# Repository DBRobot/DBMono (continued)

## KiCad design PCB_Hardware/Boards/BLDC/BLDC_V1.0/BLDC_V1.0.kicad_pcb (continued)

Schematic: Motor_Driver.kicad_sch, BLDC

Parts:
C15: 1u; C_0603_1608Metric; Manufacturer_Part_Number CC0603ZRY5V6BB105
C16: 47n; C_0805_2012Metric; Manufacturer_Part_Number CL21B473KCFNNNE
C17: 100n; C_0402_1005Metric; Manufacturer_Part_Number GRM155R62A104KE14D
C18, C19, C20: 1u; C_0402_1005Metric; Manufacturer_Part_Number CL05A105MQ5NNNC
C21: 100n; C_0402_1005Metric; Manufacturer_Part_Number CC0402ZRY5V6BB104
C22, C25, C26: 2.2u; C_0805_2012Metric; Manufacturer_Part_Number GRM21BD72A225ME01L
C23: 330u; CP_Radial_D12.5mm_P5.00mm
C28: 100n; C_0805_2012Metric; Manufacturer_Part_Number C0805C104K1RACAUTO
C47, C48, C49: ?; C_0402_1005Metric; not fitted
D15, D16, D17: SMCJ90A; D_SMC
H5, H6, H7: MountingHole_Pad; MountingHole_3.2mm_M3_DIN965_Pad
Q3, Q4, Q5, Q6, Q7, Q8: TPH3R70APL; SOP AdvanceN_TOS; Manufacturer_Part_Number TPH3R70APL
R12, R13, R14: 1m; R_2512_6332Metric; Manufacturer_Part_Number LR122WF100NT4E
R15, R16: 1k; R_0402_1005Metric; Manufacturer_Part_Number CQ02WGJ0102TCE
R32, R37, R38: 0; R_0402_1005Metric; Manufacturer_Part_Number RC0402JR-130RL
U1: DRV8353SRTAR; QFN-40-1EP_6x6mm_P0.5mm_EP4.6x4.6mm; Manufacturer_Part_Number DRV8353SRTAR

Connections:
+3.3V: R15.2, R16.2; also elsewhere on the board
+3.3VA: C20.1, C21.1, U1.24 (VREF); also elsewhere on the board
+BATT: C15.1, C17.1, C22.1, C23.1, C25.1, C26.1, C28.1, Q3.5 (D), Q3.6 (D), Q3.7 (D), Q3.8 (D), Q5.5 (D), Q5.6 (D), Q5.7 (D), Q5.8 (D), Q7.5 (D), Q7.6 (D), Q7.7 (D), Q7.8 (D), U1.3 (VM), U1.4 (VDRAIN); also elsewhere on the board
/MCU/DRIVER_CSN: U1.30 (nSCS); also elsewhere on the board
/MCU/DRIVER_MISO: R16.1, U1.27 (SDO); also elsewhere on the board
/MCU/DRIVER_MOSI: U1.28 (SDI); also elsewhere on the board
/MCU/DRIVER_SCLK: U1.29 (SCLK); also elsewhere on the board
/MCU/ENABLE: U1.31 (ENABLE); also elsewhere on the board
/MCU/INHA: U1.32 (INHA); also elsewhere on the board
/MCU/INHB: U1.34 (INHB); also elsewhere on the board
/MCU/INHC: U1.36 (INHC); also elsewhere on the board
/MCU/INLA: U1.33 (INLA); also elsewhere on the board
/MCU/INLB: U1.35 (INLB); also elsewhere on the board
/MCU/INLC: U1.37 (INLC); also elsewhere on the board
/MCU/SOA: C47.1, R38.2; also elsewhere on the board
/MCU/SOB: C48.1, R37.2; also elsewhere on the board
/MCU/SOC: C49.1, R32.2; also elsewhere on the board
/MCU/nFAULT: R15.1, U1.26 (nFAULT); also elsewhere on the board
GND: C17.2, C18.2, C19.2, C20.2, C21.2, C22.2, C23.2, C25.2, C26.2, C28.2, C47.2, C48.2, C49.2, D15.2 (A), D16.2 (A), D17.2 (A), R12.1, R13.1, R14.1, U1.10 (SNA), U1.11 (SNB), U1.20 (SNC), U1.25 (AGND), U1.39 (GND), U1.41 (PAD); also elsewhere on the board
unnamed: D15.1 (K), H5.1 (1_1), Q3.1 (S), Q3.2 (S), Q3.3 (S), Q4.5 (D), Q4.6 (D), Q4.7 (D), Q4.8 (D), U1.7 (SHA)
unnamed: D16.1 (K), H6.1 (1_1), Q5.1 (S), Q5.2 (S), Q5.3 (S), Q6.5 (D), Q6.6 (D), Q6.7 (D), Q6.8 (D), U1.14 (SHB)
unnamed: D17.1 (K), H7.1 (1_1), Q7.1 (S), Q7.2 (S), Q7.3 (S), Q8.5 (D), Q8.6 (D), Q8.7 (D), Q8.8 (D), U1.17 (SHC)
unnamed: Q3.4 (G), U1.6 (GHA)
unnamed: Q4.4 (G), U1.8 (GLA)
unnamed: Q5.4 (G), U1.15 (GHB)
unnamed: Q6.4 (G), U1.13 (GLB)
unnamed: Q7.4 (G), U1.16 (GHC)
unnamed: Q8.4 (G), U1.18 (GLC)
unnamed: C16.2, U1.2 (CPH)
unnamed: C16.1, U1.1 (CPL)
unnamed: C19.1, U1.38 (DVDD)
unnamed: R38.1, U1.23 (SOA)
unnamed: R37.1, U1.22 (SOB)
unnamed: R32.1, U1.21 (SOC)
unnamed: Q4.1 (S), Q4.2 (S), Q4.3 (S), R12.2, U1.9 (SPA)
unnamed: Q6.1 (S), Q6.2 (S), Q6.3 (S), R13.2, U1.12 (SPB)
unnamed: Q8.1 (S), Q8.2 (S), Q8.3 (S), R14.2, U1.19 (SPC)
unnamed: C15.2, U1.5 (VCP)
unnamed: C18.1, U1.40 (VGLS)

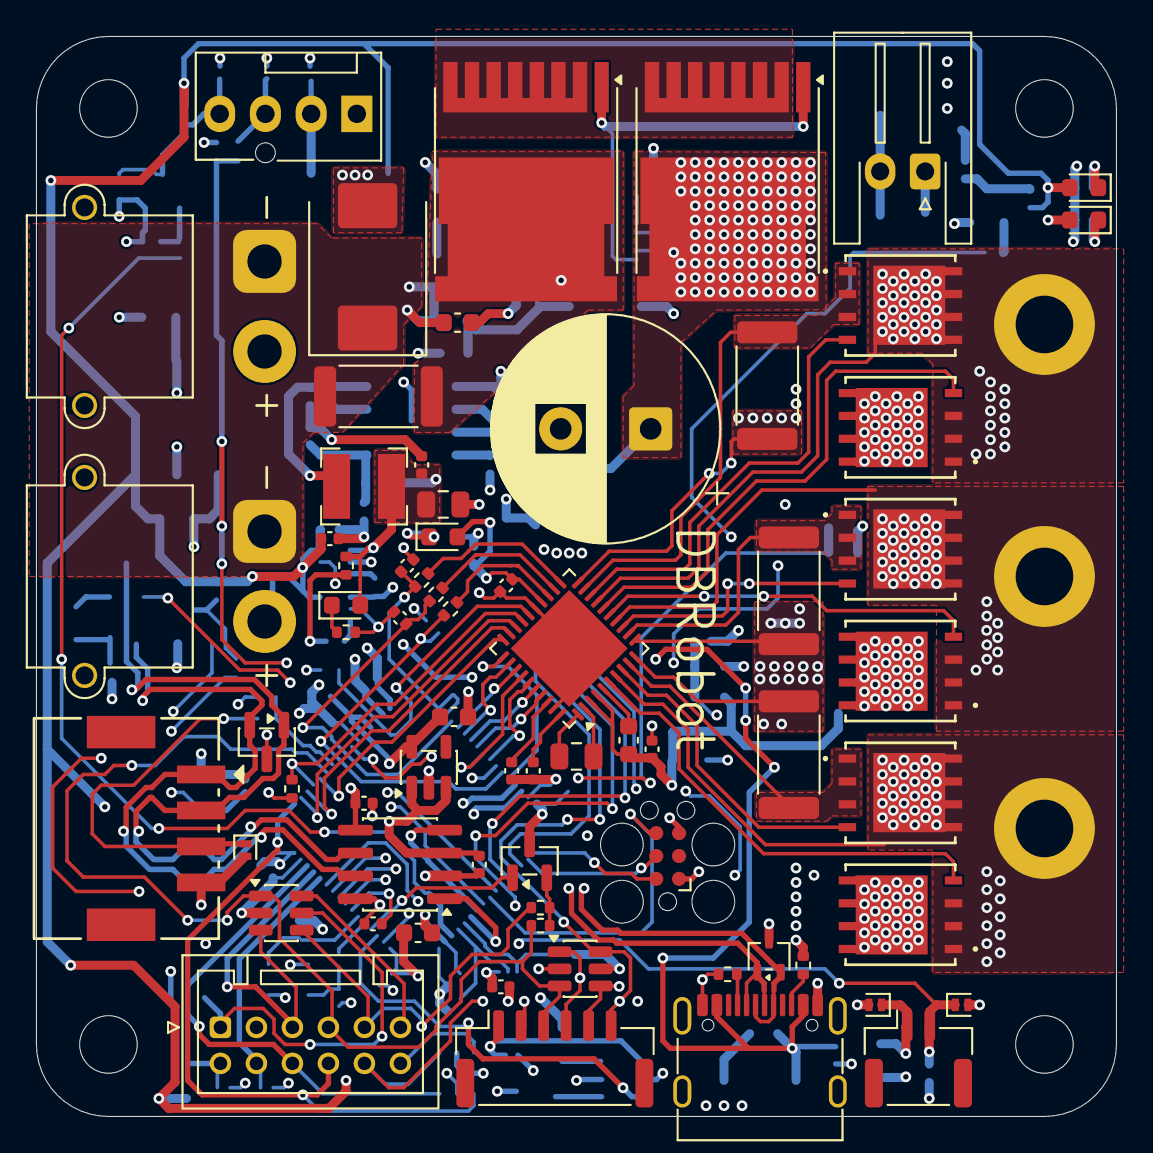
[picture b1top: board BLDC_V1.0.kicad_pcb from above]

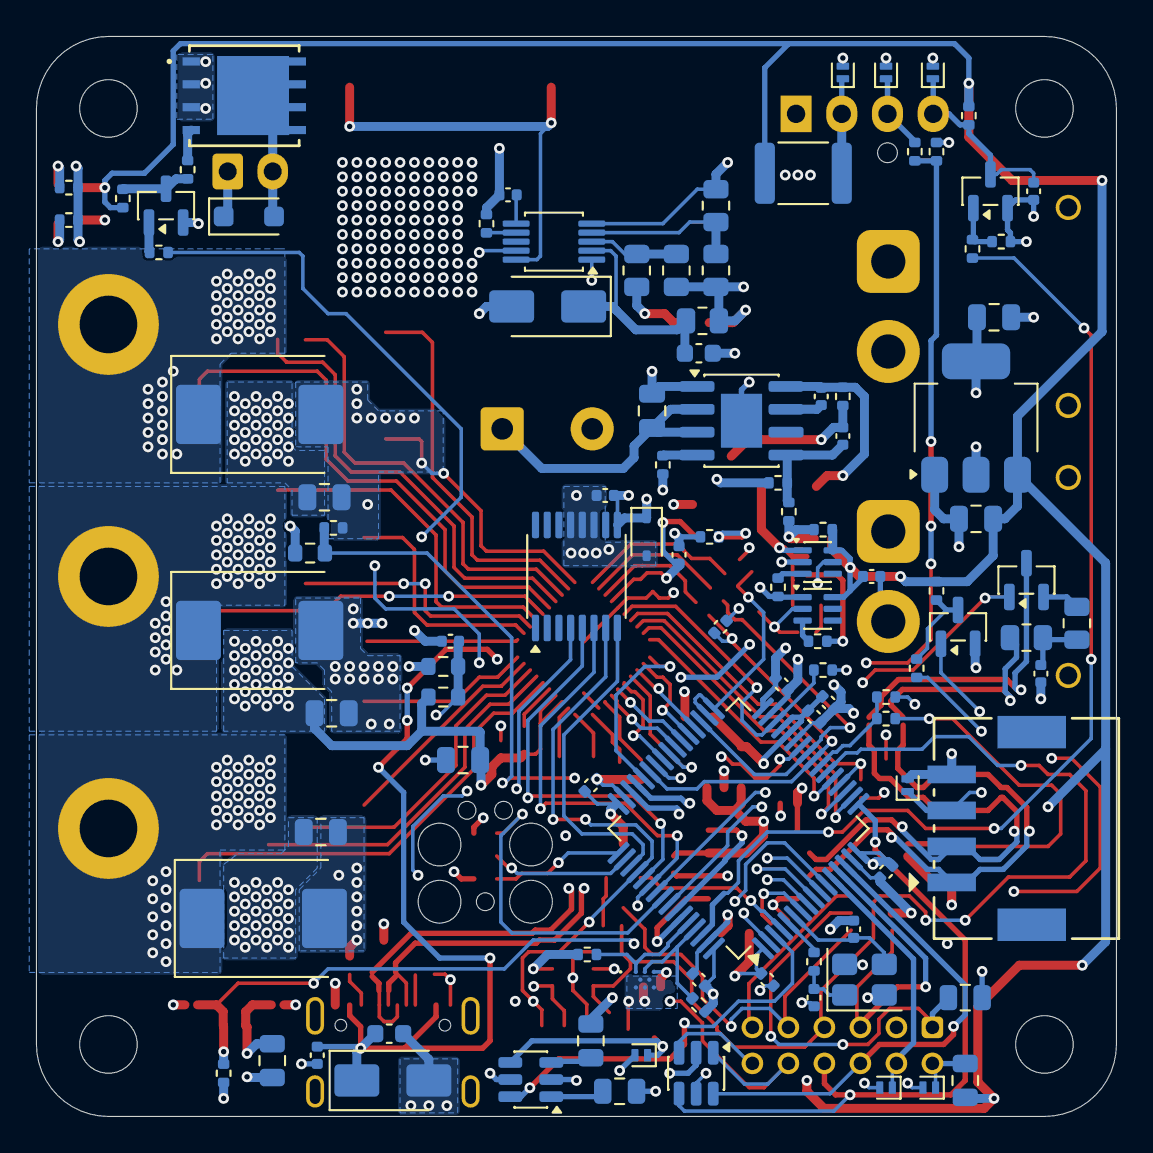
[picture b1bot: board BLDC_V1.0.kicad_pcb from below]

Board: 4 copper layers, 60.0 x 60.0 mm, 180 parts (105 on the bottom side), 122 nets.

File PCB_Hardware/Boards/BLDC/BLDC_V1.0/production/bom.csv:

Designator,Footprint,Quantity,Value,LCSC Part #
"C1, C13, C17, C2, C21, C29, C3, C31, C32, C33, C34, C35, C36, C38, C42, C45, C46, C57",0402,18,100n,
C11,0402,1,33n,
"C12, C15",0603,2,1u,
"C14, C24",0603,2,10u,
C16,0805,1,47n,
"C18, C19, C20",0402,3,1u,
"C22, C25, C26, C50",0805,4,2.2u,
C23,CP_Radial_D12.5mm_P5.00mm,1,330u,
C28,0805,1,100n,
"C30, C37",0603,2,4.7u,
C39,0402,1,10u,
C4,0402,1,47n,
"C40, C41, C54",0805,3,22u,
"C43, C44",0402,2,18p,C52923
C51,0402,1,2.2n,
C52,0402,1,3.3n,
C53,0402,1,56p,
D1,D_SOD-323,1,SD05T1G,
D10,D_SMA,1,SMAJ5.0A,
"D11, D12, D13, D21",0603,4,RED,
"D14, D19, D20, D7",D_SOD-882,4,PESD5V0L1UL,
"D15, D16, D17",D_SMC,3,SMCJ90A,
D18,D_SMA,1,BZG05C75-M3-08,
D2,SOT-23,1,PESD1CAN,
"D22, D24",D_SOD-882,2,PESD5V0S1UL,
"D23, D6, D8, D9",D_SOD-882,4,PESD3V3S1UL,
D4,D_SMC,1,SMCJ78A,
D5,D_SOD-123F,1,SS10150,
"F1, F2, F3, F4, F5",0805,5,MF-PSMF050X-2,
F6,1812,1,MF-PSMF050X-2,
"J1, J2",CONN_JST_SM04B-PASS,2,Conn_01x04_Pin,
J11,USB_C_Receptacle_G-Switch_GT-USB-7010ASV,1,GT-USB-7010ASV,
J14,FanPinHeader_1x04_P2.54mm_Vertical,1,47053-1000,
"J3, J4",AMASS_XT30PW-M_1x02_P2.50mm_Horizontal,2,Conn_01x02_Pin,
J5,JST_XH_S2B-XH-A-1_1x02_P2.50mm_Horizontal,1,Conn_01x02_Socket,
J6,JST_GH_SM02B-GHS-TB_1x02-1MP_P1.25mm_Horizontal,1,Conn_01x02_Socket,
J8,JST_PUD_B12B-PUDSS_2x06_P2.00mm_Vertical,1,Conn_02x06_Odd_Even,
J9,JST_GH_SM06B-GHS-TB_1x06-1MP_P1.25mm_Horizontal,1,Conn_01x06_Socket,
L1,L_Bourns-SRN4018,1,68u SRN4018-680M,
"Q1, Q14",SOT-23,2,SI2302,
Q10,SOT-23,1,BC847,
Q11,SOT-23,1,BSS138,
Q12,SOT-23,1,BSS84,
"Q13, Q2",Infineon_PG-HSOF-8-1,2,IPT015N10N5,
"Q3, Q4, Q5, Q6, Q7, Q8, Q9",SOP AdvanceN_TOS,7,TPH3R70APL,
"R1, R2",0805,2,60,
R10,0805,1,3.9k,
R11,0402,1,3.9k,
"R12, R13, R14",2512,3,1m,
"R15, R16, R20, R36, R60",0402,5,1k,
R17,0603,1,100k,
"R18, R22, R23, R35, R58, R59",0402,6,10k,
R19,0402,1,4.7,
R21,0603,1,4.7k,
"R24, R32, R37, R38",0402,4,0,
"R25, R26, R27, R28",0402,4,4.7k,
R29,0805,1,49,
R30,0402,1,24.9k,
R31,0402,1,121k,
R33,0402,1,1.8k,
R34,0402,1,3.3k,
R39,0402,1,453k,
R40,0402,1,143k,
"R47, R48",0402,2,5.1k,
"R49, R52, R53, R54, R57",0402,5,100k,
R50,0402,1,5k,
"R51, R55, R61",0402,3,2.2k,
R56,0402,1,100,
R6,2512,1,0.5m,
R7,0805,1,102k,
R8,0805,1,30k,
R9,0805,1,113k,
TH1,0603,1,Thermistor,
U1,QFN-40-1EP_6x6mm_P0.5mm_EP4.6x4.6mm,1,DRV8353SRTAR,
U10,SOT-323_SC-70,1,TPD2E2U06DCK,
U11,SOT-223-3_TabPin2,1,AMS1117-3.3,
"U12, U13",SOT-363_SC-70-6,2,LM66100DCK,
"U14, U8, U9",SOT-23-6,3,SRV05-4,
U15,SOT-23-6,1,TS5A3159ADBVR,
U16,CAT24C512C8UTR,1,CAT24C512C8UTR,
U2,TSSOP-16_4.4x5mm_P0.65mm,1,MT6835GT-STD,
U3,SOIC-8_3.9x4.9mm_P1.27mm,1,TCAN1044VDR,
U4,SOIC-8-1EP_3.9x4.9mm_P1.27mm_EP2.29x3mm,1,~,
U5,MSOP-10_3x3mm_P0.5mm,1,LM5069MM-2,
U6,SOT-23-5,1,TLV70233_SOT23-5,
U7,LQFP-64_10x10mm_P0.5mm,1,STM32G474RET6,
Y2,Crystal_SMD_3225-4Pin_3.2x2.5mm,1,XXGBBCNANF-25.000000MHZ,

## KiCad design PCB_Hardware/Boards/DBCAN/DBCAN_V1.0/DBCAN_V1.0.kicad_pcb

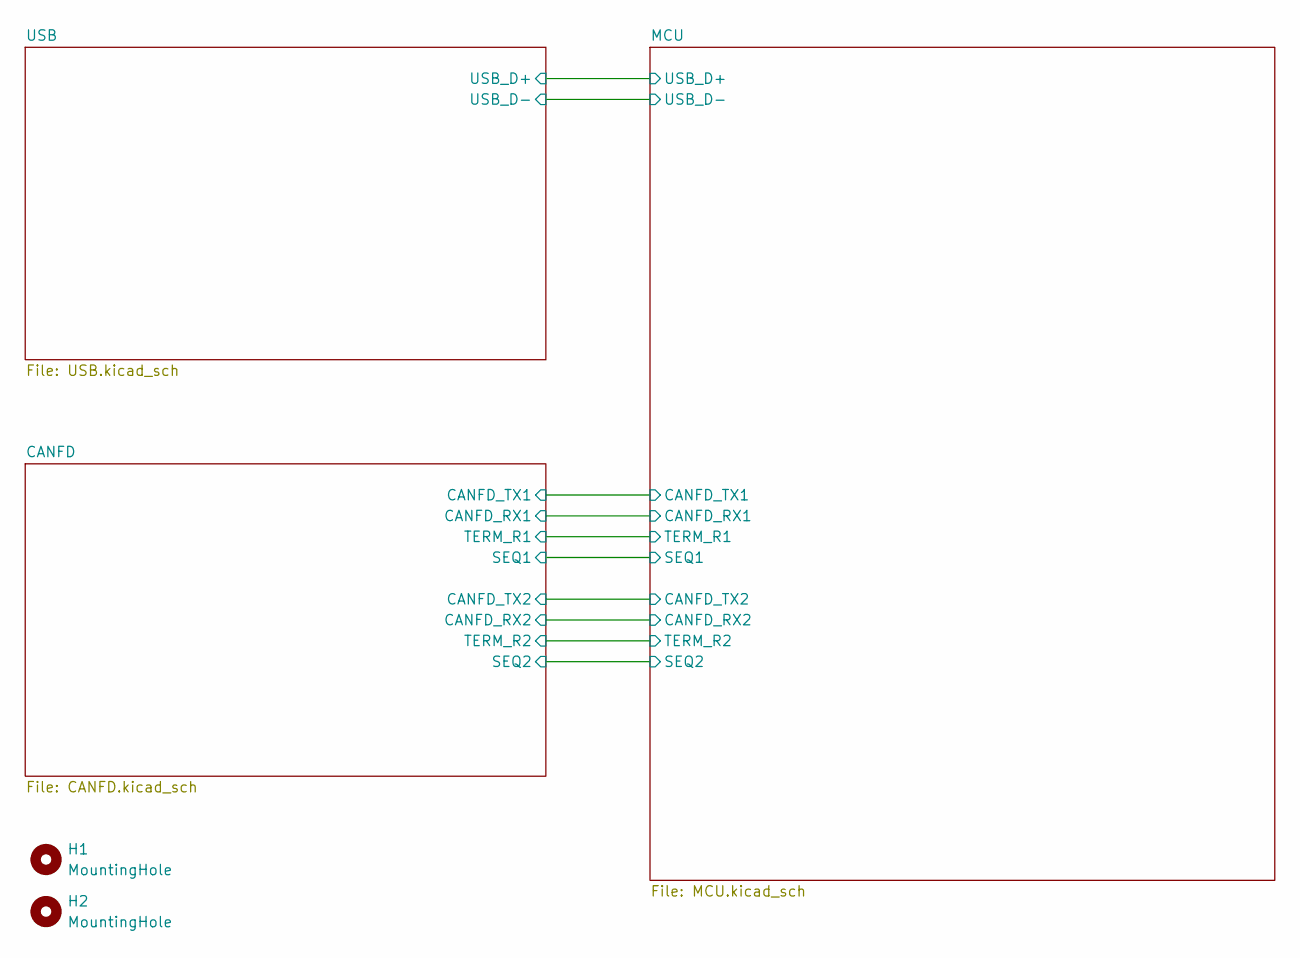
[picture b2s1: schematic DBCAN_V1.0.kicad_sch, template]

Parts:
H1, H2: MountingHole; MountingHole_3.2mm_M3

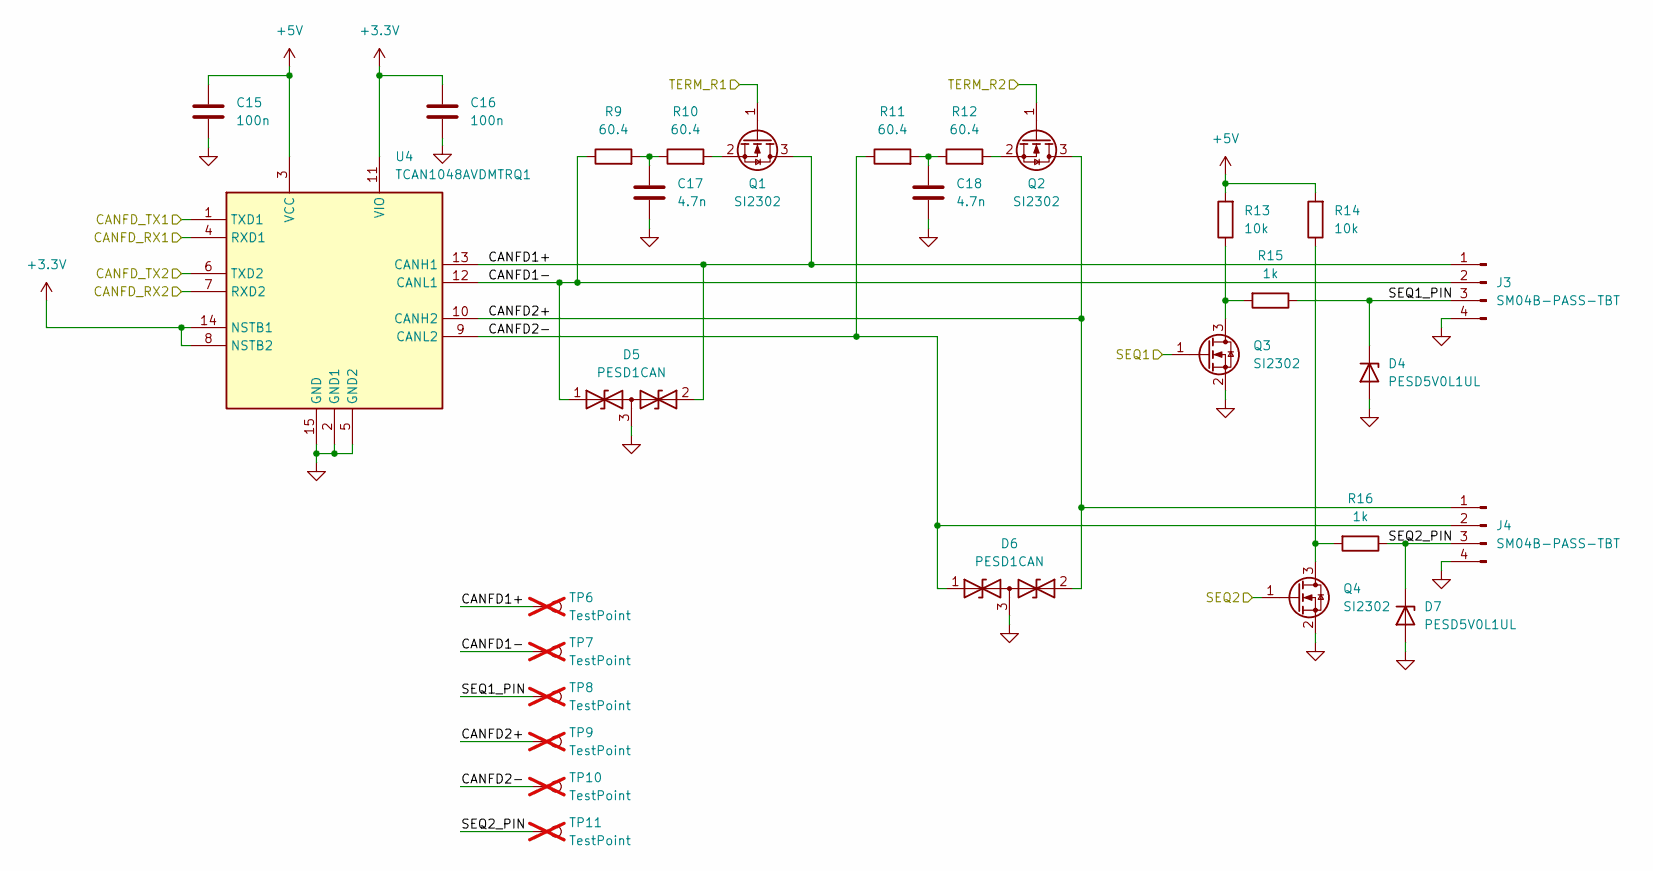
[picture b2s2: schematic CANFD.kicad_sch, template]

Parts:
C15, C16: 100n; C_0402_1005Metric; Manufacturer_Part_Number CC0402KRX7R7BB104
C17, C18: 4.7n; C_0402_1005Metric; Manufacturer_Part_Number CC0402KRX7R9BB472
D4, D7: PESD5V0L1UL; D_SOD-882; Manufacturer_Part_Number PESD5V0L1UL
D5, D6: PESD1CAN; SOT-23; Manufacturer_Part_Number PESD1CAN
J3, J4: SM04B-PASS-TBT; CONN_JST_SM04B-PASS; Manufacturer_Part_Number SM04B-PASS-TBT
Q1, Q2, Q3, Q4: SI2302; SOT-23; Manufacturer_Part_Number Si2302CDS-T1-GE3
R9, R10, R11, R12: 60.4; R_0805_2012Metric; Manufacturer_Part_Number RC0805FR-0760R4L
R13, R14: 10k; R_0402_1005Metric; Manufacturer_Part_Number RC0402JR-1310KL
R15, R16: 1k; R_0402_1005Metric; Manufacturer_Part_Number AC0402JR-071KL
TP6, TP7, TP8, TP9, TP10, TP11: TestPoint; TestPoint_Pad_D1.0mm; not fitted
U4: TCAN1048AVDMTRQ1; DFN-14-1EP_3x4.5mm_P0.65mm_EP1.65x4.25mm; Mouser Part Number 595-TCAN1048AVDMTRQ1

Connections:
+3.3V: C16.1, U4.8 (NSTB2), U4.11 (VIO), U4.14 (NSTB1); also elsewhere on the board
+5V: C15.1, R13.2, R14.2, U4.3 (VCC); also elsewhere on the board
/CANFD/CANFD1+: D5.2 (A2), J3.1, Q1.3 (D), TP6.1 (1_1), U4.13 (CANH1)
/CANFD/CANFD1-: D5.1 (A1), J3.2, R9.1, TP7.1 (1_1), U4.12 (CANL1)
/CANFD/CANFD2+: D6.2 (A2), J4.1, Q2.3 (D), TP9.1 (1_1), U4.10 (CANH2)
/CANFD/CANFD2-: D6.1 (A1), J4.2, R11.1, TP10.1 (1_1), U4.9 (CANL2)
/CANFD/CANFD_RX1: U4.4 (RXD1); also elsewhere on the board
/CANFD/CANFD_RX2: U4.7 (RXD2); also elsewhere on the board
/CANFD/CANFD_TX1: U4.1 (TXD1); also elsewhere on the board
/CANFD/CANFD_TX2: U4.6 (TXD2); also elsewhere on the board
/CANFD/SEQ1: Q3.1 (G); also elsewhere on the board
/CANFD/SEQ1_PIN: D4.1 (K), J3.3, R15.1, TP8.1 (1_1)
/CANFD/SEQ2: Q4.1 (G); also elsewhere on the board
/CANFD/SEQ2_PIN: D7.1 (K), J4.3, R16.1, TP11.1 (1_1)
/CANFD/TERM_R1: Q1.1 (G); also elsewhere on the board
/CANFD/TERM_R2: Q2.1 (G); also elsewhere on the board
GND: C15.2, C16.2, C17.2, C18.2, D4.2 (A), D5.3 (common), D6.3 (common), D7.2 (A), J3.4, J4.4, Q3.2 (S), Q4.2 (S), U4.2 (GND1), U4.5 (GND2), U4.15 (GND); also elsewhere on the board
unnamed: C17.1, R9.2, R10.1
unnamed: C18.1, R11.2, R12.1
unnamed: Q1.2 (S), R10.2
unnamed: Q2.2 (S), R12.2
unnamed: Q3.3 (D), R13.1, R15.2
unnamed: Q4.3 (D), R14.1, R16.2

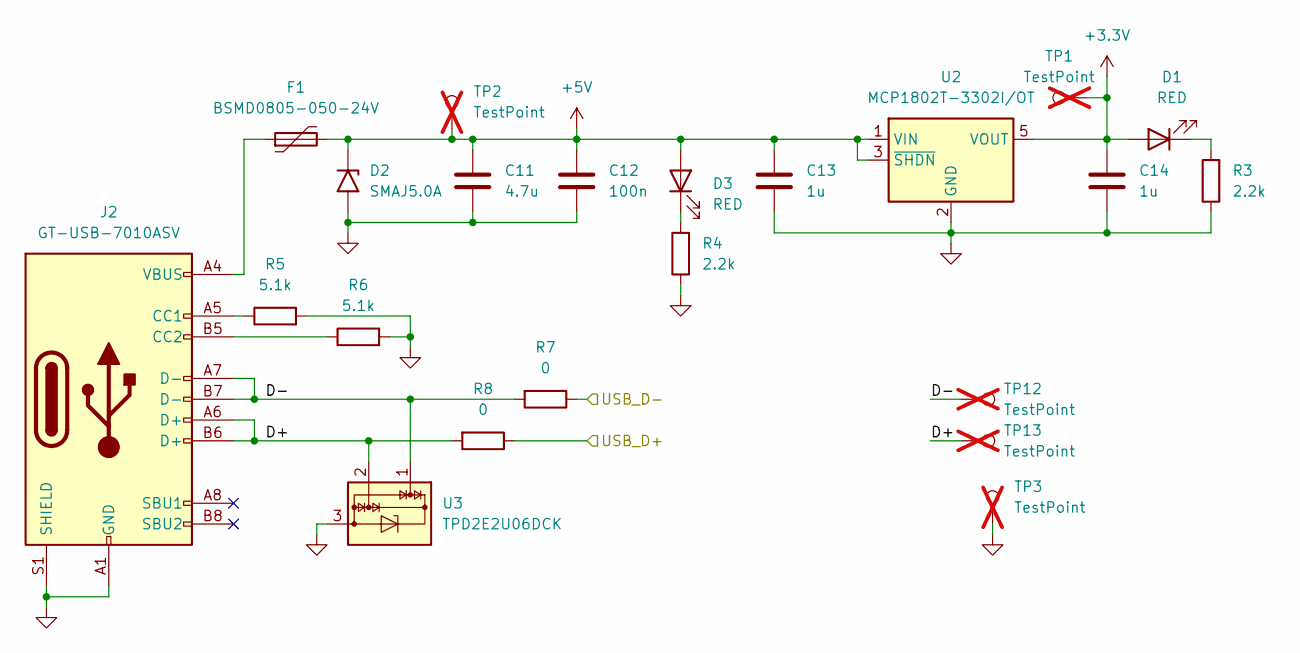
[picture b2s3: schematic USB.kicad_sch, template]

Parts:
C11: 4.7u; C_0603_1608Metric; Manufacturer_Part_Number CL10A475KO8NNNC
C12: 100n; C_0402_1005Metric; Manufacturer_Part_Number CC0402KRX7R7BB104
C13, C14: 1u; C_0603_1608Metric; Manufacturer_Part_Number CL10B105KA8NNNC
D1, D3: RED; LED_0603_1608Metric; Manufacturer_Part_Number XL-1608VRC-06
D2: SMAJ5.0A; D_SMA; Manufacturer_Part_Number SMAJ5.0A
F1: BSMD0805-050-24V; Fuse_0805_2012Metric; Manufacturer_Part_Number BSMD0805-050-24V
J2: GT-USB-7010ASV; USB_C_Receptacle_G-Switch_GT-USB-7010ASV; Manufacturer_Part_Number GT-USB-7010ASV
R3, R4: 2.2k; R_0402_1005Metric; Manufacturer_Part_Number RC0402FR-075M9L
R5, R6: 5.1k; R_0402_1005Metric; Manufacturer_Part_Number RC0402JR-075K1L
R7, R8: 0; R_0402_1005Metric; Manufacturer_Part_Number RC0402JR-070RL
TP1, TP2, TP3, TP12, TP13: TestPoint; TestPoint_Pad_D1.0mm; not fitted
U2: MCP1802T-3302I/OT; SOT-23-5; Manufacturer_Part_Number MCP1802T-3302I/OT
U3: TPD2E2U06DCK; SOT-323_SC-70; Manufacturer_Part_Number TPD2E2U06DCKR

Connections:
+3.3V: C14.1, D1.2 (A), TP1.1 (1_1), U2.5 (VOUT); also elsewhere on the board
+5V: C11.1, C12.1, C13.1, D2.1 (A1), D3.2 (A), F1.2, TP2.1 (1_1), U2.1 (VIN), U2.3 (~SHDN); also elsewhere on the board
/MCU/USB_D+: R8.1; also elsewhere on the board
/MCU/USB_D-: R7.1; also elsewhere on the board
/USB/D+: J2.A6 (D+), J2.B6 (D+), R8.2, TP13.1 (1_1), U3.2
/USB/D-: J2.A7 (D-), J2.B7 (D-), R7.2, TP12.1 (1_1), U3.1
GND: C11.2, C12.2, C13.2, C14.2, D2.2 (A2), J2.A1 (GND), J2.A12 (GND), J2.B1 (GND), J2.B12 (GND), J2.S1 (SHIELD), R3.1, R4.1, R5.2, R6.2, TP3.1 (1_1), U2.2 (GND), U3.3; also elsewhere on the board
unnamed: D1.1 (K), R3.2
unnamed: D3.1 (K), R4.2
unnamed: F1.1, J2.A4 (VBUS), J2.A9 (VBUS), J2.B4 (VBUS), J2.B9 (VBUS)
unnamed: J2.A5 (CC1), R5.1
unnamed: J2.B5 (CC2), R6.1

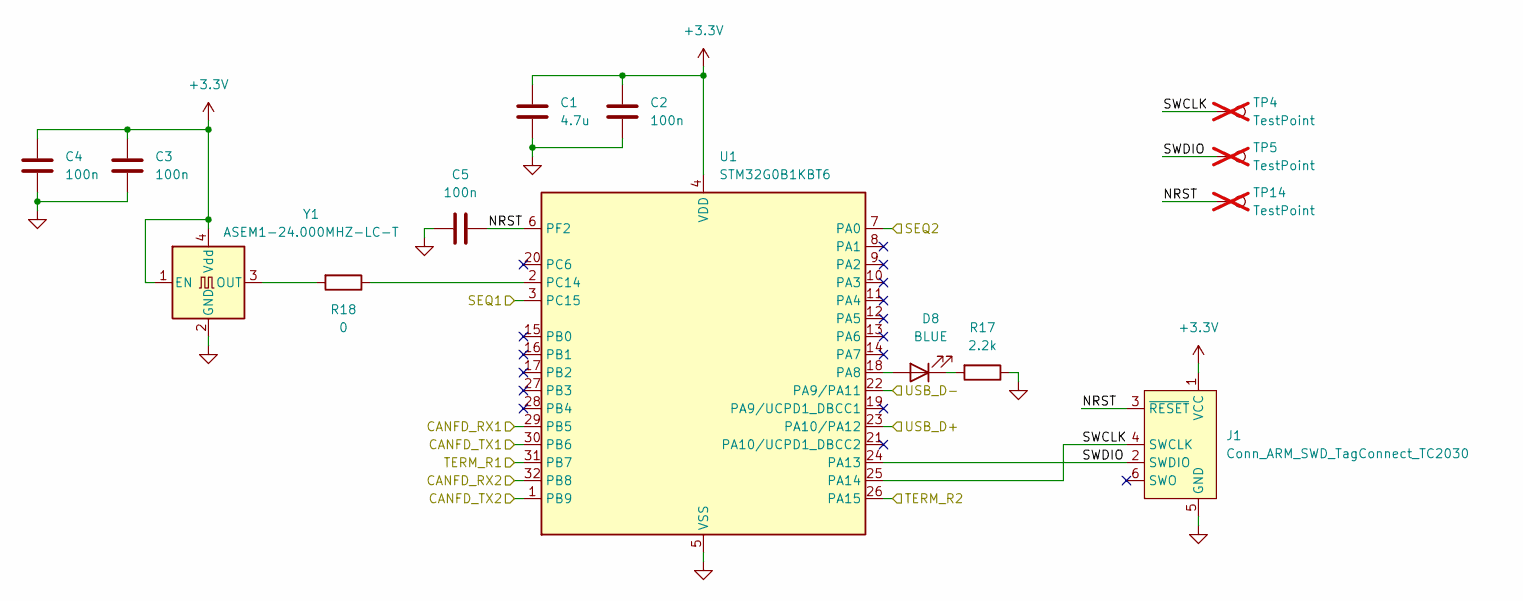
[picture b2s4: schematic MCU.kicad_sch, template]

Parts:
C1: 4.7u; C_0603_1608Metric; Manufacturer_Part_Number CL10A475KO8NNNC
C2, C3, C4, C5: 100n; C_0402_1005Metric; Manufacturer_Part_Number CC0402KRX7R7BB104
D8: BLUE; LED_0603_1608Metric; Manufacturer_Part_Number XL-1608UBC-06A
J1: Conn_ARM_SWD_TagConnect_TC2030; Tag-Connect_TC2030-IDC-FP_2x03_P1.27mm_Vertical
R17: 2.2k; R_0402_1005Metric; Manufacturer_Part_Number RC0402FR-075M9L
R18: 0; R_0402_1005Metric; Manufacturer_Part_Number RC0402JR-070RL
TP4, TP5, TP14: TestPoint; TestPoint_Pad_D1.0mm; not fitted
U1: STM32G0B1KBT6; LQFP-32_7x7mm_P0.8mm; Manufacturer_Part_Number STM32G0B1KBT6
Y1: ASEM1-24.000MHZ-LC-T; Oscillator_SMD_Abracon_ASE-4Pin_3.2x2.5mm; Manufacturer_Part_Number ASEM1-24.000MHZ-LC-T

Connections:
+3.3V: C1.1, C2.1, C3.1, C4.1, J1.1 (VCC), U1.4 (VDD), Y1.1 (EN), Y1.4 (Vdd); also elsewhere on the board
/CANFD/CANFD_RX1: U1.29 (PB5); also elsewhere on the board
/CANFD/CANFD_RX2: U1.32 (PB8); also elsewhere on the board
/CANFD/CANFD_TX1: U1.30 (PB6); also elsewhere on the board
/CANFD/CANFD_TX2: U1.1 (PB9); also elsewhere on the board
/CANFD/SEQ1: U1.3 (PC15); also elsewhere on the board
/CANFD/SEQ2: U1.7 (PA0); also elsewhere on the board
/CANFD/TERM_R1: U1.31 (PB7); also elsewhere on the board
/CANFD/TERM_R2: U1.26 (PA15); also elsewhere on the board
/MCU/NRST: C5.2, J1.3 (~RESET), TP14.1 (1_1), U1.6 (PF2)
/MCU/SWCLK: J1.4 (SWCLK), TP4.1 (1_1), U1.25 (PA14)
/MCU/SWDIO: J1.2 (SWDIO), TP5.1 (1_1), U1.24 (PA13)
/MCU/USB_D+: U1.23 (PA10/PA12); also elsewhere on the board
/MCU/USB_D-: U1.22 (PA9/PA11); also elsewhere on the board
GND: C1.2, C2.2, C3.2, C4.2, C5.1, J1.5 (GND), R17.1, U1.5 (VSS), Y1.2 (GND); also elsewhere on the board
unnamed: D8.2 (A), U1.18 (PA8)
unnamed: D8.1 (K), R17.2
unnamed: R18.1, U1.2 (PC14)
unnamed: R18.2, Y1.3 (OUT)

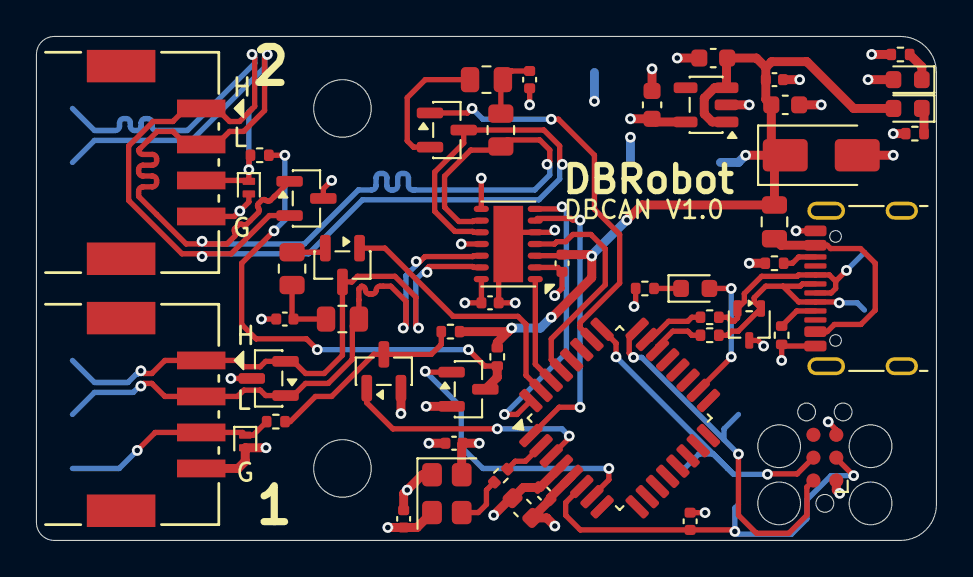
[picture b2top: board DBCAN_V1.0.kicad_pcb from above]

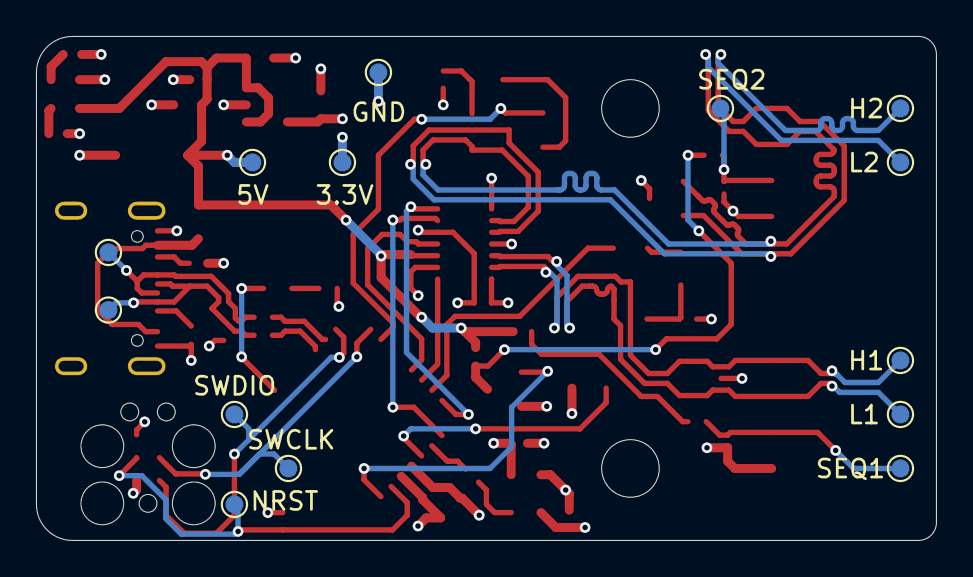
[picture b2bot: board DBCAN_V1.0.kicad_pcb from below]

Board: 4 copper layers, 50.0 x 28.0 mm, 67 parts (14 on the bottom side), 39 nets.

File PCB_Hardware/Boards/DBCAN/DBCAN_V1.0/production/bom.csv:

Designator,Footprint,Quantity,Value,LCSC Part #
"C1, C11",0603,2,4.7u,
"C12, C15, C16, C2, C3, C4, C5",0402,7,100n,
"C13, C14",0603,2,1u,
"C17, C18",0402,2,4.7n,
"D1, D3",0603,2,RED,
D2,D_SMA,1,SMAJ5.0A,
"D4, D7",D_SOD-882,2,PESD5V0L1UL,
"D5, D6",SOT-23,2,PESD1CAN,
D8,0603,1,BLUE,
F1,0805,1,BSMD0805-050-24V,
J2,USB_C_Receptacle_G-Switch_GT-USB-7010ASV,1,GT-USB-7010ASV,
"J3, J4",CONN_JST_SM04B-PASS,2,SM04B-PASS-TBT,
"Q1, Q2, Q3, Q4",SOT-23,4,SI2302,
"R10, R11, R12, R9",0805,4,60.4,
"R13, R14",0402,2,10k,
"R15, R16",0402,2,1k,
"R17, R3, R4",0402,3,2.2k,
"R18, R7, R8",0402,3,0,
"R5, R6",0402,2,5.1k,
U1,LQFP-32_7x7mm_P0.8mm,1,STM32G0B1KBT6,
U2,SOT-23-5,1,MCP1802T-3302I/OT,
U3,SOT-323_SC-70,1,TPD2E2U06DCK,
U4,DFN-14-1EP_3x4.5mm_P0.65mm_EP1.65x4.25mm,1,TCAN1048AVDMTRQ1,
Y1,Oscillator_SMD_Abracon_ASE-4Pin_3.2x2.5mm,1,ASEM1-24.000MHZ-LC-T,

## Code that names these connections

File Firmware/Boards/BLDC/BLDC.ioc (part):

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Mcu.Name=STM32G474R(B-C-E)Tx
Mcu.Package=LQFP64
Mcu.UserName=STM32G474RETx
PA10.GPIOParameters=GPIO_Label
PA10.GPIO_Label=ENABLE
PA10.Signal=GPIO_Output
PA11.Mode=Device
PA11.Signal=USB_DM
PA12.Mode=Device
PA12.Signal=USB_DP
PA13.Mode=Trace_Asynchronous_SW
PA13.Signal=SYS_JTMS-SWDIO
PA14.Mode=Trace_Asynchronous_SW
PA14.Signal=SYS_JTCK-SWCLK
PA15.GPIOParameters=GPIO_Label
PA15.GPIO_Label=DRIVER_CSN
PA15.Signal=GPIO_Output
PA4.GPIOParameters=GPIO_Label
PA4.GPIO_Label=ENCODER_CSN
PA4.Signal=GPIO_Output
PA5.Mode=Full_Duplex_Master
PA5.Signal=SPI1_SCK
PA6.Mode=Full_Duplex_Master
PA6.Signal=SPI1_MISO
PA7.Mode=Full_Duplex_Master
PA7.Signal=SPI1_MOSI
PA9.Mode=IN2-Single-Ended
PA9.Signal=ADC5_IN2
PB0.Mode=INP
PB0.Signal=COMP4_INP
PB1.Mode=INP
PB1.Signal=COMP1_INP
PB10.Mode=Fault_Enable3
PB10.Signal=HRTIM1_FLT3
PB11.Mode=INP
PB11.Signal=COMP6_INP
PB12.Mode=IN3-Single-Ended
PB12.Signal=ADC4_IN3
PB13.Mode=IN5-Single-Ended
PB13.Signal=ADC3_IN5
PB14.Mode=Output_TD1TD2
PB14.Signal=HRTIM1_CHD1
PB15.Mode=Output_TD1TD2
PB15.Signal=HRTIM1_CHD2
PB2.GPIOParameters=GPIO_Label
PB2.GPIO_Label=BREAK
PB2.Signal=S_TIM20_CH1
PB3.Mode=Trace_Asynchronous_SW
PB3.Signal=SYS_JTDO-SWO
PB4.GPIOParameters=GPIO_Label
PB4.GPIO_Label=FAN_TACH
PB4.Signal=S_TIM16_CH1
PB5.Mode=FDCAN_Activate
PB5.Signal=FDCAN2_RX
PB6.Mode=FDCAN_Activate
PB6.Signal=FDCAN2_TX
PB7.Mode=I2C
PB7.Signal=I2C1_SDA
PB8-BOOT0.Mode=I2C
PB8-BOOT0.Signal=I2C1_SCL
PB9.GPIOParameters=GPIO_Label
PB9.GPIO_Label=FAN_PWM
PB9.Signal=S_TIM17_CH1
PC0.Mode=IN6-Single-Ended
PC0.Signal=ADC1_IN6
PC1.Mode=IN7-Single-Ended
PC1.Signal=ADC1_IN7
PC10.Mode=Full_Duplex_Master
PC10.Signal=SPI3_SCK
PC11.Mode=Full_Duplex_Master
PC11.Signal=SPI3_MISO
PC12.Mode=Full_Duplex_Master
PC12.Signal=SPI3_MOSI
PC2.Mode=IN8-Single-Ended
PC2.Signal=ADC1_IN8
PC3.Mode=IN9-Single-Ended
PC3.Signal=ADC1_IN9
PC6.Mode=Output_TF1TF2
PC6.Signal=HRTIM1_CHF1
PC7.Mode=Output_TF1TF2
PC7.Signal=HRTIM1_CHF2
PC8.Mode=Output_TE1TE2
PC8.Signal=HRTIM1_CHE1
PC9.Mode=Output_TE1TE2
PC9.Signal=HRTIM1_CHE2
PF0-OSC_IN.Mode=HSE-External-Oscillator
PF0-OSC_IN.Signal=RCC_OSC_IN
PF1-OSC_OUT.Mode=HSE-External-Oscillator
PF1-OSC_OUT.Signal=RCC_OSC_OUT
RCC.HSE_VALUE=25000000
RCC.SYSCLKFreq_VALUE=160000000
RCC.SYSCLKSource=RCC_SYSCLKSOURCE_PLLCLK
board=custom

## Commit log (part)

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2026-03-28 added KiCAD file templetes based on JLCPCB capabilities
2026-03-28 Add a setup script for the repo and KiCAD Symlink for the kicad template
2026-03-28 add README.md
2026-03-31 - Add BLDC schematic draft for V1.0 - Add .ioc file from cubemx for the mcu pin out - Add kicad custom symbol lib - Update kicad templates - Update gitignore for cubemx metadata and .bak files from k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
2026-03-31 Removed external temp sensing bc I forgot the calibration enable pin for the encoder
2026-03-31 redid external temp sensing and instead removed V Bus sense from the USBC input
2026-03-31 foget to add the GPIO to change the voltage for AUX2 SPI port, removed the ability to pull AUX pins down to free a pin
2026-04-01 Adding a Claude skill to help review PCB designs
2026-04-02 planning ID headers for DBcan
2026-04-02 format
2026-04-12 Add schematic-review, kicad-cli, and spice-sim skills
    Three new Claude Code skills for PCB/schematic development:
    - schematic-review: 7-agent parallel design review for KiCad schematics
    - kicad-cli: comprehensive kicad-cli command reference and recipes
    - spice-sim: ngspice simulation generation from KiCad schematics
2026-04-13 Adds the design for a USB to canfd 2 channel converter
2026-04-13 Remove duplicate dir
2026-04-15 Completed board layout and tweaks to schematic. Added 3D model lib
2026-04-15 Switch license from GPL-3.0 to CERN-OHL-S-2.0
    Covers hardware designs, firmware, and software under a single
    strongly-reciprocal open hardware license.
2026-04-15 Switch license from CERN-OHL-S-2.0 to CERN-OHL-W-2.0
2026-04-18 Base driver for FDCAN. has init, tx and rx
2026-04-18 Restructure Firmware layout; CMSIS as proper submodules
    - Move CMSIS to Firmware/libs/ (shared by bootloader + future app)
    - Reorganize into Protocols/DBcan/{Bootloader,core}
    - Add fdcan_deinit() via RCC APB1RSTR1 peripheral reset
    - Fix TX/RX index masks (were dropping LSB for 3-buffer counts)
    - Add G4 filter capacity guards (28 SID / 8 XID)
    - Remove unused defines from canfd.h
2026-05-03 First version of DBCAN board
2026-05-03 Add DBCAN V1.0 board, KiCAD templates/libs, PCB review skill
2026-05-03 Remove redundant pcb-review skill (superseded by schematic-review)
2026-05-03 Make KiCad library paths portable via ${DBMONO_LIBS} env var
    - DBCAN fp-lib-table, sym-lib-table, and 3D model paths now use ${DBMONO_LIBS}
    - KiCAD_template includes DBRobot lib entries so new boards inherit them
    - setup.sh writes DBMONO_LIBS into kicad_common.json for all KiCad versions
    - Drop unused tools/vscode-c-block-comment symlink from setup.sh
    - Rename TCAN1048 STEP to short filename
2026-05-18 Add DBcan transport refactor, BLDC V1.0 schematic + sim work, HAL submodule
    - DBcan: replace bare-register driver with vendor-agnostic transport abstraction (core/, transports/, refactored bootloader driver, README)
    - Add stm32g4xx_hal_driver as Firmware/libs submodule
    - Add HAL config for BLDC board (stm32g4xx_hal_conf.h)
    - BLDC V1.0: schematic edits across 10 sheets (footprint assignments, repositioning); design-doc README (gate-driver constraints, FET selection / TPH3R70APL, thermal analysis)
    - ngspice simulation workflow (cap sweeps, half-bridge slow turn-on)
    - Ignore .obsidian/ vault state and large simulation CSV exports
2026-05-18 Add SPICE model libs and full waveform CSVs; remove generic *.lib ignore
    - Drop *.lib from .gitignore (it was a generic C-build-output rule that was silently catching SPICE model files, which share the .lib extension)
    - Add tph3r70apl.lib and drv8353_gate_driver.lib to BLDC sim dir (TPH3R70APL FET and DRV8353 gate driver models referenced by the .cir netlists)
    - Drop the simulation/*.csv ignore rule and commit power.csv and waves_A_Original_2x150_wet.csv as canonical waveform captures
2026-05-23 migrated claude skills to opencode, and added to the schematic review skill. Also updated the readme with calculations for the BLDC driver and changed the sense resistors to 1m Ohm
2026-05-25 Created organization around the symbol lib and did a first pass layout of the BDLC
2026-05-26 complete redo of the BLDC layout
2026-05-30 layout revision of the BLDC
2026-05-30 moved Protocols folder to the root dir. completed the first version of the can transport port to stm32. started a port to socketcan
